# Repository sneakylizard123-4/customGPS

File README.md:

# customGPS
A custom GPS and compass board for 5" drones.

## How to use
connect to power. GPS uses UART and compass uses I2C.
solder capacitor to "cap here"

# Pictures
blender render:

PCB:

Schematic:

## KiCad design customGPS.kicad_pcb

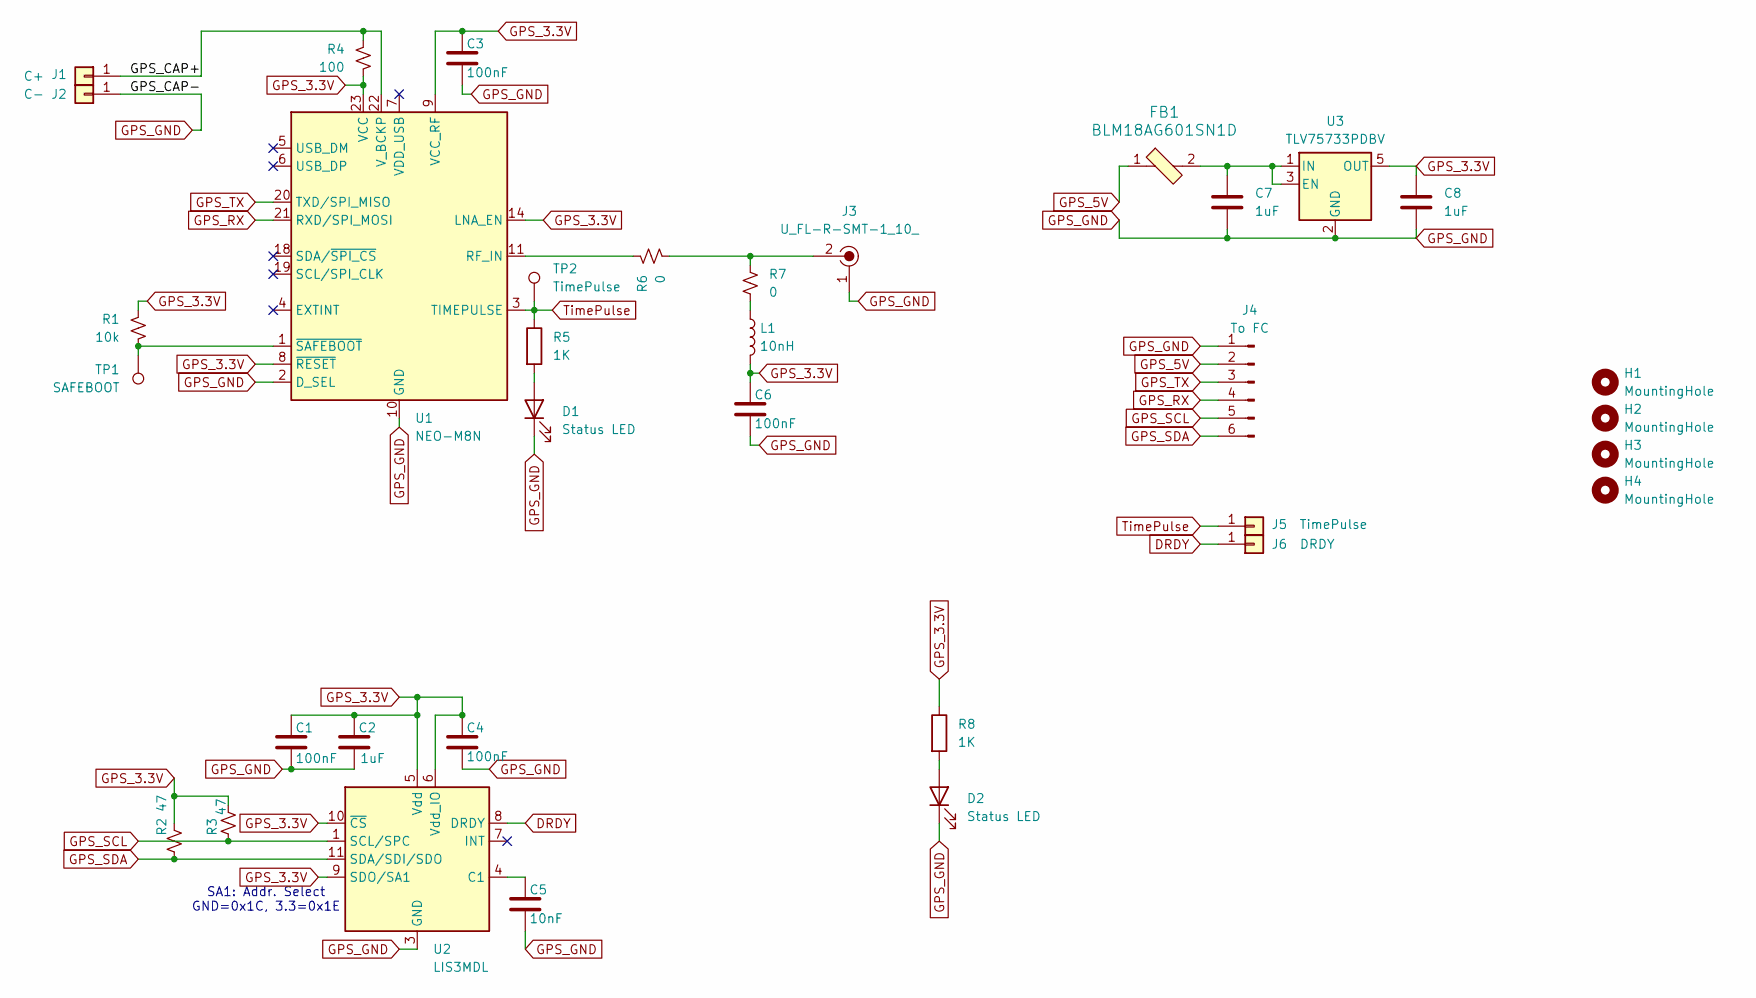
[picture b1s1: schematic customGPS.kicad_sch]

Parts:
C1, C3, C4, C6: 100nF; C_0805_2012Metric_Pad1.18x1.45mm_HandSolder
C2, C7, C8: 1uF; C_0805_2012Metric_Pad1.18x1.45mm_HandSolder
C5: 10nF; C_0805_2012Metric_Pad1.18x1.45mm_HandSolder
D1, D2: Status LED; LED_0603_1608Metric_Pad1.05x0.95mm_HandSolder
FB1: BLM18AG601SN1D; 0603; MPN BLM18AG601SN1D; Digi-Key_PN 490-1014-1-ND
H1, H2, H3, H4: MountingHole; MountingHole_3.2mm_M3
J1: C+; SolderWirePad_1x01_SMD_1x2mm
J2: C-; SolderWirePad_1x01_SMD_1x2mm
J3: U_FL-R-SMT-1_10_; U.FL_Molex_MCRF_73412-0110_Vertical; MPN U.FL-R-SMT-1(10); Digi-Key_PN H11891CT-ND
J4: To FC; Hirose_DF13-06P-1.25DS_1x06_P1.25mm_Horizontal
J5: TimePulse; SolderWirePad_1x01_SMD_1x2mm
J6: DRDY; SolderWirePad_1x01_SMD_1x2mm
L1: 10nH; L_0805_2012Metric_Pad1.05x1.20mm_HandSolder
R1: 10k; R_0805_2012Metric_Pad1.20x1.40mm_HandSolder
R2, R3: 47; R_0805_2012Metric_Pad1.20x1.40mm_HandSolder
R4: 100; R_0805_2012Metric_Pad1.20x1.40mm_HandSolder
R5, R8: 1K; R_0805_2012Metric_Pad1.20x1.40mm_HandSolder
R6, R7: 0; R_0805_2012Metric_Pad1.20x1.40mm_HandSolder
TP1: SAFEBOOT; TestPoint_Pad_1.0x1.0mm
TP2: TimePulse; TestPoint_Pad_1.0x1.0mm
U1: NEO-M8N; ublox_NEO
U2: LIS3MDL; LGA-12_2x2mm_P0.5mm
U3: TLV75733PDBV; SOT-23-5

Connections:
/GPS_CAP+: J1.1, R4.1, U1.22 (V_BCKP)
DRDY: J6.1, U2.8 (DRDY)
GPS_3.3V: C1.1, C2.1, C3.1, C4.1, C6.1, C8.1, L1.2, R1.1, R2.1, R3.2, R4.2, R8.1, U1.8 (~RESET), U1.9 (VCC_RF), U1.14 (LNA_EN), U1.23 (VCC), U2.5 (Vdd), U2.6 (Vdd_IO), U2.9 (SDO/SA1), U2.10 (~CS), U3.5 (OUT)
GPS_5V: FB1.1, J4.2
GPS_GND: C1.2, C2.2, C3.2, C4.2, C5.2, C6.2, C7.2, C8.2, D1.1 (K), D2.1 (K), J2.1, J3.1, J4.1, U1.2 (D_SEL), U1.10 (GND), U1.12 (GND), U1.13 (GND), U1.24 (GND), U2.2 (GND), U2.3 (GND), U2.12 (GND), U3.2 (GND)
GPS_RX: J4.4, U1.21 (RXD/SPI_MOSI)
GPS_SCL: J4.5, R3.1, U2.1 (SCL/SPC)
GPS_SDA: J4.6, R2.2, U2.11 (SDA/SDI/SDO)
GPS_TX: J4.3, U1.20 (TXD/SPI_MISO)
unnamed: D1.2 (A), R5.2
unnamed: D2.2 (A), R8.2
unnamed: J3.2, R6.2, R7.1
unnamed: L1.1, R7.2
unnamed: R6.1, U1.11 (RF_IN)
unnamed: R1.2, TP1.1, U1.1 (~SAFEBOOT)
unnamed: C5.1, U2.4 (C1)
unnamed: C7.1, FB1.2, U3.1 (IN), U3.3 (EN)
TimePulse: J5.1, R5.1, TP2.1, U1.3 (TIMEPULSE)

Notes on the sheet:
SA1: Addr. Select GND=0x1C, 3.3=0x1E

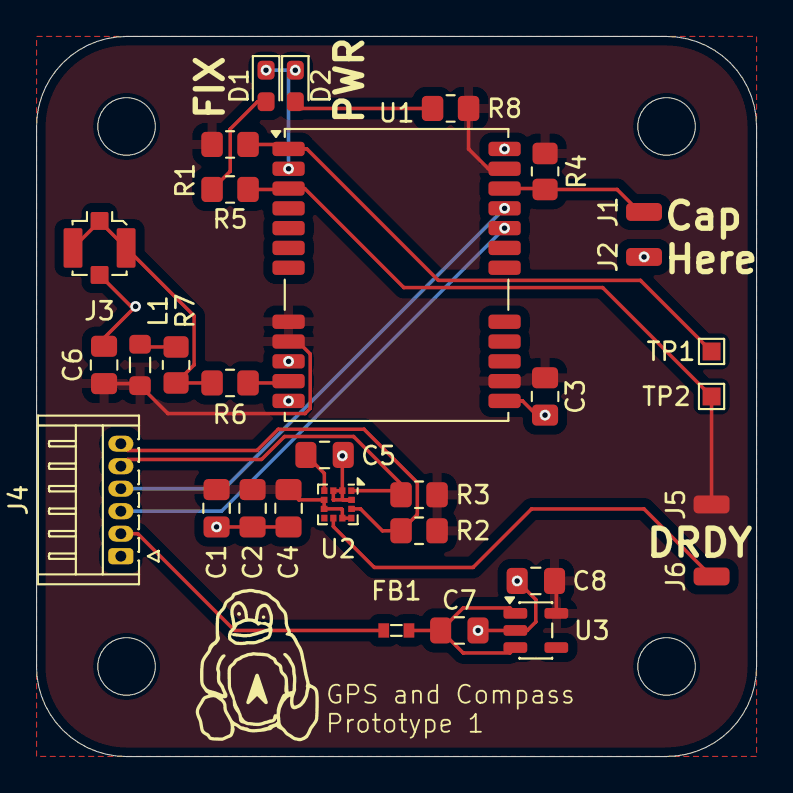
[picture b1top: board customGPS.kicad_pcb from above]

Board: 2 copper layers, 40.0 x 40.0 mm, 35 parts (0 on the bottom side), 18 nets.

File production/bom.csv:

Designator,Footprint,Quantity,Value,LCSC Part #
"C1, C3, C4, C6",0805,4,100nF,
"C2, C7, C8",0805,3,1uF,
C5,0805,1,10nF,
"D1, D2",0603,2,Status LED,
FB1,0603,1,BLM18AG601SN1D,BLM18AG601SN1D
J1,SolderWirePad_1x01_SMD_1x2mm,1,C+,
J2,SolderWirePad_1x01_SMD_1x2mm,1,C-,
J3,U.FL_Molex_MCRF_73412-0110_Vertical,1,U_FL-R-SMT-1_10_,U.FL-R-SMT-1(10)
J4,Hirose_DF13-06P-1.25DS_1x06_P1.25mm_Horizontal,1,To FC,
J6,SolderWirePad_1x01_SMD_1x2mm,1,DRDY,
L1,0805,1,10nH,
R1,0805,1,10k,
"R2, R3",0805,2,47,
R4,0805,1,100,
"R5, R8",0805,2,1K,
"R6, R7",0805,2,0,
TP1,TestPoint_Pad_1.0x1.0mm,1,SAFEBOOT,
TP2,TestPoint_Pad_1.0x1.0mm,1,TimePulse,
U1,ublox_NEO,1,NEO-M8N,
U2,LGA-12_2x2mm_P0.5mm,1,LIS3MDL,
U3,SOT-23-5,1,TLV75733PDBV,

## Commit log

2026-01-27 files
2026-01-28 gerbers
2026-01-28 add readme file
2026-01-28 Initialize README with project details
    Added basic project description and usage instructions.
2026-01-28 add pcb3d export
2026-01-28 add blender render
2026-01-28 add blend file
2026-01-28 Enhance README with images and formatting
    Added images for the PCB and schematic to the README.
2026-01-29 update pcb and fix drc errors
2026-02-01 Update README with capacitor soldering instructions
    Added instructions to solder capacitor to the documentation.
